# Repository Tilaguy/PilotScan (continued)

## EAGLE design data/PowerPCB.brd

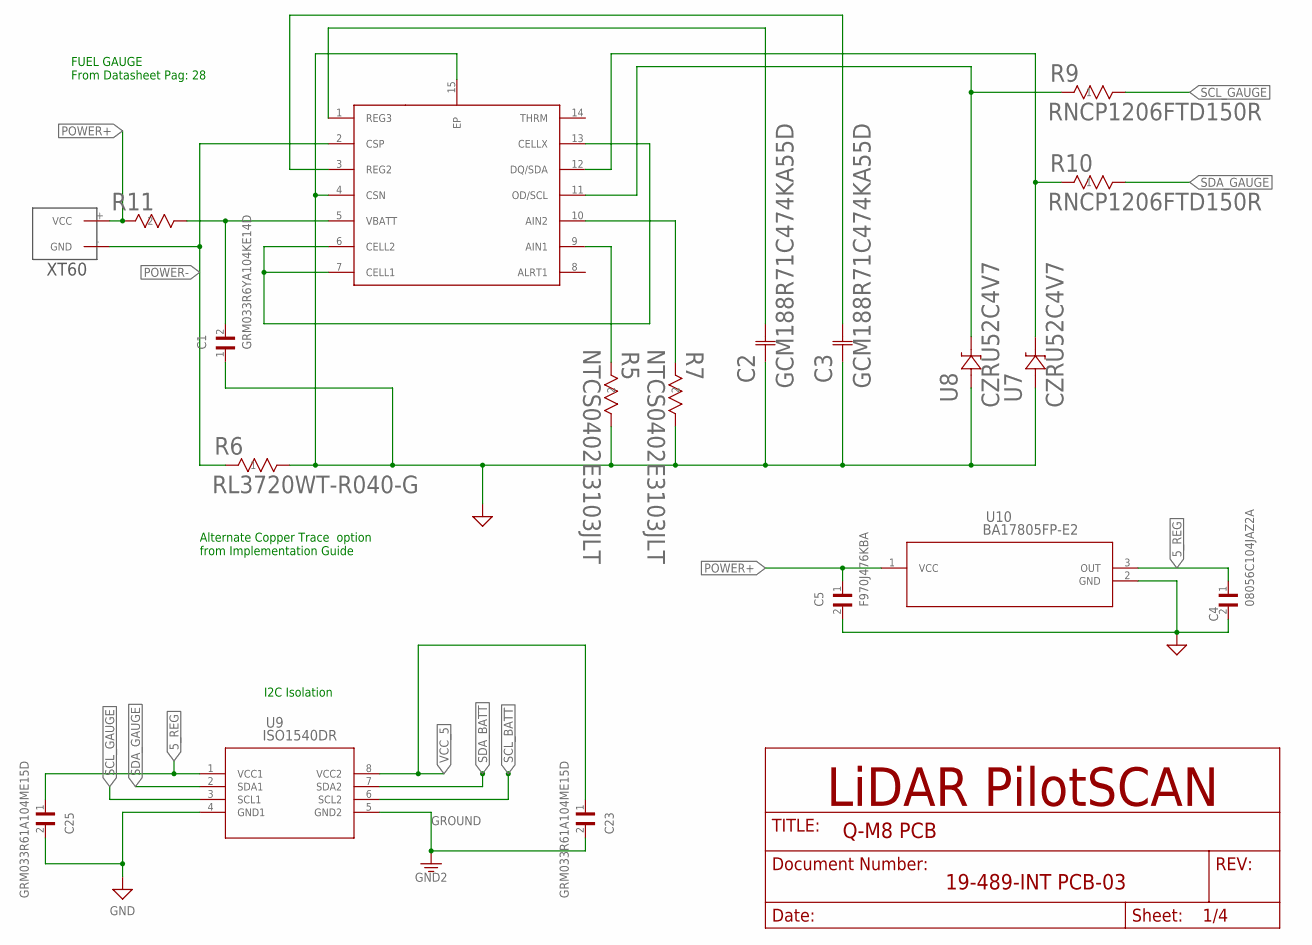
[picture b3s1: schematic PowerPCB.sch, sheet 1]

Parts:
C1: GRM033R6YA104KE14D; CAPC0603X33N
C2, C3: GCM188R71C474KA55D; G-188
C4: 08056C104JAZ2A; CAPC2012X140N
C5: F970J476KBA; CAPPC3528X210N
C23, C25: GRM033R61A104ME15D; CAPC0603X33N
J5: XT60
R5, R7: NTCS0402E3103JLT; RES_0402_NTC
R6: RL3720WT-R040-G; RES_2037
R9, R10: RNCP1206FTD150R; STA_RNCP1206
R11: ERA-2AKD100X; RC0402N
U5: MAX17205G+T
U7, U8: CZRU52C4V7; CZRU
U9: ISO1540DR; D8
U10: BA17805FP-E2; TO252-3

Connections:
5_REG: C4.1, C25.1, U9.1 (VCC1), U10.3 (OUT); also elsewhere on the board
GND: C1.1, C2.1, C3.1, C4.2, C5.2, C25.2, R5.1, R6.2, R7.1, U5.4 (CSN), U5.15 (EP), U7.2, U8.2, U9.4 (GND1), U10.2 (GND); also elsewhere on the board
GROUND: C23.2, U9.5 (GND2); also elsewhere on the board
unnamed: C1.2, R11.1, U5.5 (VBATT)
unnamed: R5.2, U5.9 (AIN1)
unnamed: C2.2, U5.1 (REG3)
unnamed: R7.2, U5.10 (AIN2)
unnamed: C3.2, U5.3 (REG2)
unnamed: U5.6 (CELL2), U5.7 (CELL1), U5.13 (CELLX)
unnamed: R9.1, U5.11 (OD/SCL), U8.1
unnamed: R10.1, U5.12 (DQ/SDA), U7.1
POWER+: C5.1, J5.+ (VCC), R11.2, U10.1 (VCC); also elsewhere on the board
POWER-: J5.- (GND), R6.1, U5.2 (CSP)
SCL_BATT: U9.6 (SCL2); also elsewhere on the board
SCL_GAUGE: R9.2, U9.3 (SCL1)
SDA_BATT: U9.7 (SDA2); also elsewhere on the board
SDA_GAUGE: R10.2, U9.2 (SDA1)
VCC_5: C23.1, U9.8 (VCC2); also elsewhere on the board

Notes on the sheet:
FUEL GAUGE From Datasheet Pag: 28
I2C Isolation
Alternate Copper Trace option from Implementation Guide

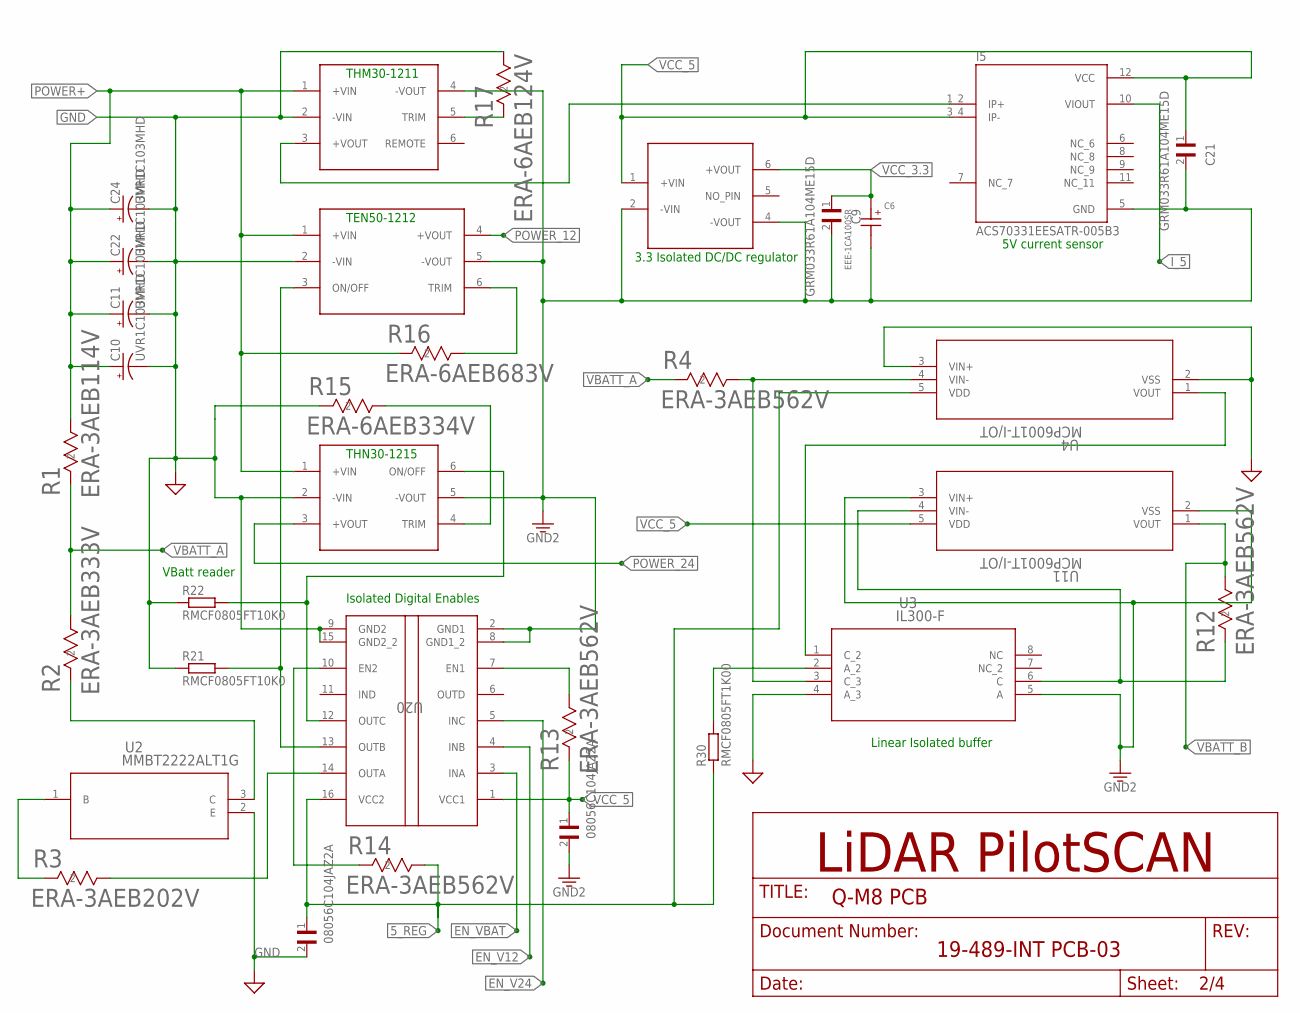
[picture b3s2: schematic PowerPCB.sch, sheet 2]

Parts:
C6: EEE-1CA100SR; CAPAE430X550N
C7, C8: 08056C104JAZ2A; CAPC2012X140N
C9, C21: GRM033R61A104ME15D; CAPC0603X33N
C10, C11, C22, C24: UVR1C103MHD; U1-PP
DCDC5: THM30-1211
DCDC12: TEN50-1212
DCDC24: THN30-1215
I5: ACS70331EESATR-005B3; ACS70331EESATR-2P5U3
R1: ERA-3AEB114V; RC0603N
R2: ERA-3AEB333V; RC0603N
R3: ERA-3AEB202V; RC0603N
R4, R12, R13, R14: ERA-3AEB562V; RC0603N
R15: ERA-6AEB334V; RC0805N
R16: ERA-6AEB683V; RC0805N
R17: ERA-6AEB124V; RC0805N
R21, R22: RMCF0805FT10K0
R30: RMCF0805FT1K00
U2: MMBT2222ALT1G; SOT-23
U3: IL300-F; DIP8_IL
U4, U11: MCP6001T-I/OT; SOT-23-5_MC
U6: TMV0503SHI
U20: ISO7741DBQR; DBQ0016A_N

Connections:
5_REG: C8.1, R14.1, R30.1, U4.5 (VDD), U20.16 (VCC2); also elsewhere on the board
EN_V12: U20.4 (INB); also elsewhere on the board
EN_V24: U20.5 (INC); also elsewhere on the board
EN_VBAT: U20.3 (INA); also elsewhere on the board
GND: C8.2, C10.2 (-), C11.2 (-), C22.2 (-), C24.2 (-), DCDC5.2 (-VIN), DCDC12.2 (-VIN), DCDC24.2 (-VIN), R15.2, R17.1, R21.1, R22.1, U2.2 (E), U3.4 (A_3), U4.2 (VSS), U4.3 (VIN+), U20.9 (GND2), U20.15 (GND2_2); also elsewhere on the board
GROUND: C6.2, C7.2, C9.2, C21.2, DCDC5.4 (-VOUT), DCDC12.5 (-VOUT), DCDC24.5 (-VOUT), I5.5 (GND), U3.5 (A), U6.2 (-VIN), U6.4 (-VOUT), U11.2 (VSS), U11.3 (VIN+), U20.2 (GND1), U20.8 (GND1_2); also elsewhere on the board
I_5: I5.10 (VIOUT); also elsewhere on the board
unnamed: R13.1, U20.7 (EN1)
unnamed: R3.2, U2.1 (B)
unnamed: R2.2, U2.3 (C)
unnamed: R4.1, U3.3 (C_3), U4.4 (VIN-)
unnamed: DCDC12.3 (ON/OFF), R21.2, U20.13 (OUTB)
unnamed: R30.2, U3.2 (A_2)
unnamed: R14.2, U20.10 (EN2)
unnamed: U3.1 (C_2), U4.1 (VOUT)
unnamed: R12.2, U3.6 (C), U11.4 (VIN-)
unnamed: DCDC24.6 (ON/OFF), R22.2, U20.12 (OUTC)
unnamed: R3.1, U20.14 (OUTA)
unnamed: DCDC5.5 (TRIM), R17.2
unnamed: DCDC24.4 (TRIM), R15.1
unnamed: DCDC12.6 (TRIM), R16.1
POWER+: C10.1 (+), C11.1 (+), C22.1 (+), C24.1 (+), DCDC5.1 (+VIN), DCDC12.1 (+VIN), DCDC24.1 (+VIN), R1.1, R16.2; also elsewhere on the board
POWER_5: DCDC5.3 (+VOUT), I5.1_2 (IP+)
POWER_12: DCDC12.4 (+VOUT); also elsewhere on the board
POWER_24: DCDC24.3 (+VOUT); also elsewhere on the board
VBATT_A: R1.2, R2.1, R4.2
VBATT_B: R12.1, U11.1 (VOUT); also elsewhere on the board
VCC_3.3: C6.1, C9.1, U6.6 (+VOUT); also elsewhere on the board
VCC_5: C7.1, C21.1, I5.3_4 (IP-), I5.12 (VCC), R13.2, U6.1 (+VIN), U11.5 (VDD), U20.1 (VCC1); also elsewhere on the board

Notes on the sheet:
Isolated Digital Enables
Linear Isolated buffer
5V current sensor
3.3 Isolated DC/DC regulator
VBatt reader
THM30-1211
THN30-1215
TEN50-1212

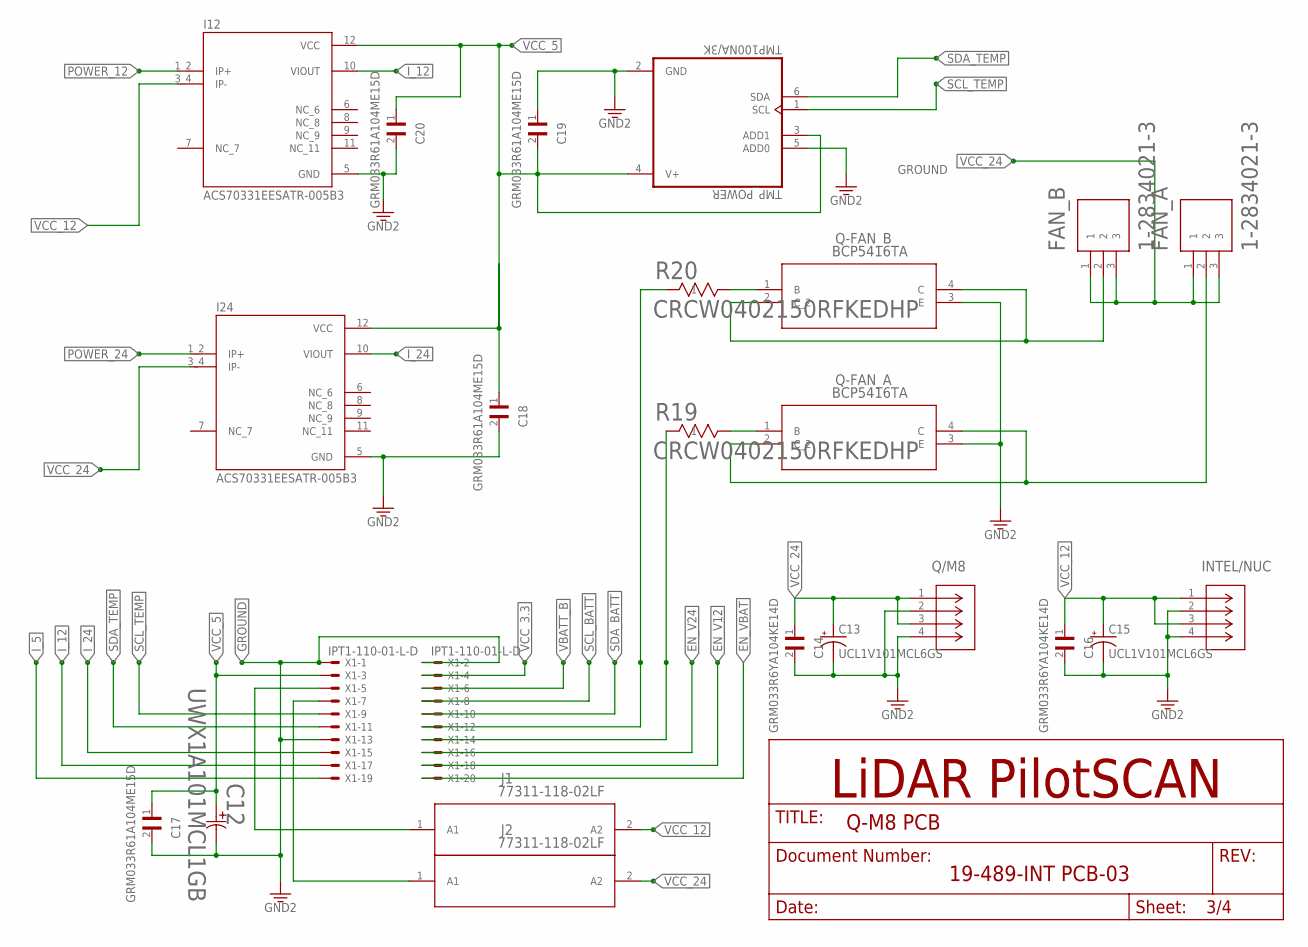
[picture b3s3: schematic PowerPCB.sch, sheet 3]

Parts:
C12: UWX1A101MCL1GB; PCAP_6.3X5.4-ELECT
C13, C15: UCL1V101MCL6GS; U2-K
C14, C16: GRM033R6YA104KE14D; CAPC0603X33N
C17, C18, C19, C20: GRM033R61A104ME15D; CAPC0603X33N
FAN_A: 1-2834021-3; CONN_1-2834021-3
FAN_B: 1-2834021-3; CONN_1-2834021-3
I12, I24: ACS70331EESATR-005B3; ACS70331EESATR-2P5U3
INTEL/NUC: 3-794630-4; CON4_2X2_P3MM_VMNL2
J1, J2: 77311-118-02LF
Q-FAN_A: BCP5416TA; SOT-223
Q-FAN_B: BCP5416TA; SOT-223
Q/M8: 3-794630-4; CON4_2X2_P3MM_VMNL2
R19, R20: CRCW0402150RFKEDHP; RES_CRCW_0402
TMP_POWER: TMP100NA/3K
X1: IPT1-110-01-L-D

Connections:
EN_V12: X1.P$18; also elsewhere on the board
EN_V24: X1.P$16; also elsewhere on the board
EN_VBAT: X1.P$20; also elsewhere on the board
GROUND: C12.2, C13.2 (-), C14.2, C15.2 (-), C16.2, C17.2, C18.2, C19.1, C20.2, I12.5 (GND), I24.5 (GND), INTEL/NUC.2, INTEL/NUC.4, Q-FAN_A.3 (E), Q-FAN_B.3 (E), Q/M8.2, Q/M8.4, TMP_POWER.2 (GND), TMP_POWER.5 (ADD0), X1.P$1, X1.P$2, X1.P$13; also elsewhere on the board
I_5: X1.P$19; also elsewhere on the board
I_12: I12.10 (VIOUT), X1.P$17
I_24: I24.10 (VIOUT), X1.P$15
unnamed: J1.1 (A1), X1.P$5
unnamed: J2.1 (A1), X1.P$7
unnamed: FAN_A.2, Q-FAN_A.2 (C_2), Q-FAN_A.4 (C)
unnamed: R20.1, X1.P$12
unnamed: R19.1, X1.P$14
unnamed: Q-FAN_B.1 (B), R20.2
unnamed: Q-FAN_A.1 (B), R19.2
unnamed: FAN_B.2, Q-FAN_B.2 (C_2), Q-FAN_B.4 (C)
POWER_12: I12.1_2 (IP+); also elsewhere on the board
POWER_24: I24.1_2 (IP+); also elsewhere on the board
SCL_BATT: X1.P$8; also elsewhere on the board
SCL_TEMP: TMP_POWER.1 (SCL), X1.P$9
SDA_BATT: X1.P$10; also elsewhere on the board
SDA_TEMP: TMP_POWER.6 (SDA), X1.P$11
VBATT_B: X1.P$6; also elsewhere on the board
VCC_3.3: X1.P$4; also elsewhere on the board
VCC_5: C12.1, C17.1, C18.1, C19.2, C20.1, I12.12 (VCC), I24.12 (VCC), TMP_POWER.3 (ADD1), TMP_POWER.4 (V+), X1.P$3; also elsewhere on the board
VCC_12: C15.1 (+), C16.1, I12.3_4 (IP-), INTEL/NUC.1, INTEL/NUC.3, J1.2 (A2); also elsewhere on the board
VCC_24: C13.1 (+), C14.1, FAN_A.1, FAN_A.3, FAN_B.1, FAN_B.3, I24.3_4 (IP-), J2.2 (A2), Q/M8.1, Q/M8.3; also elsewhere on the board

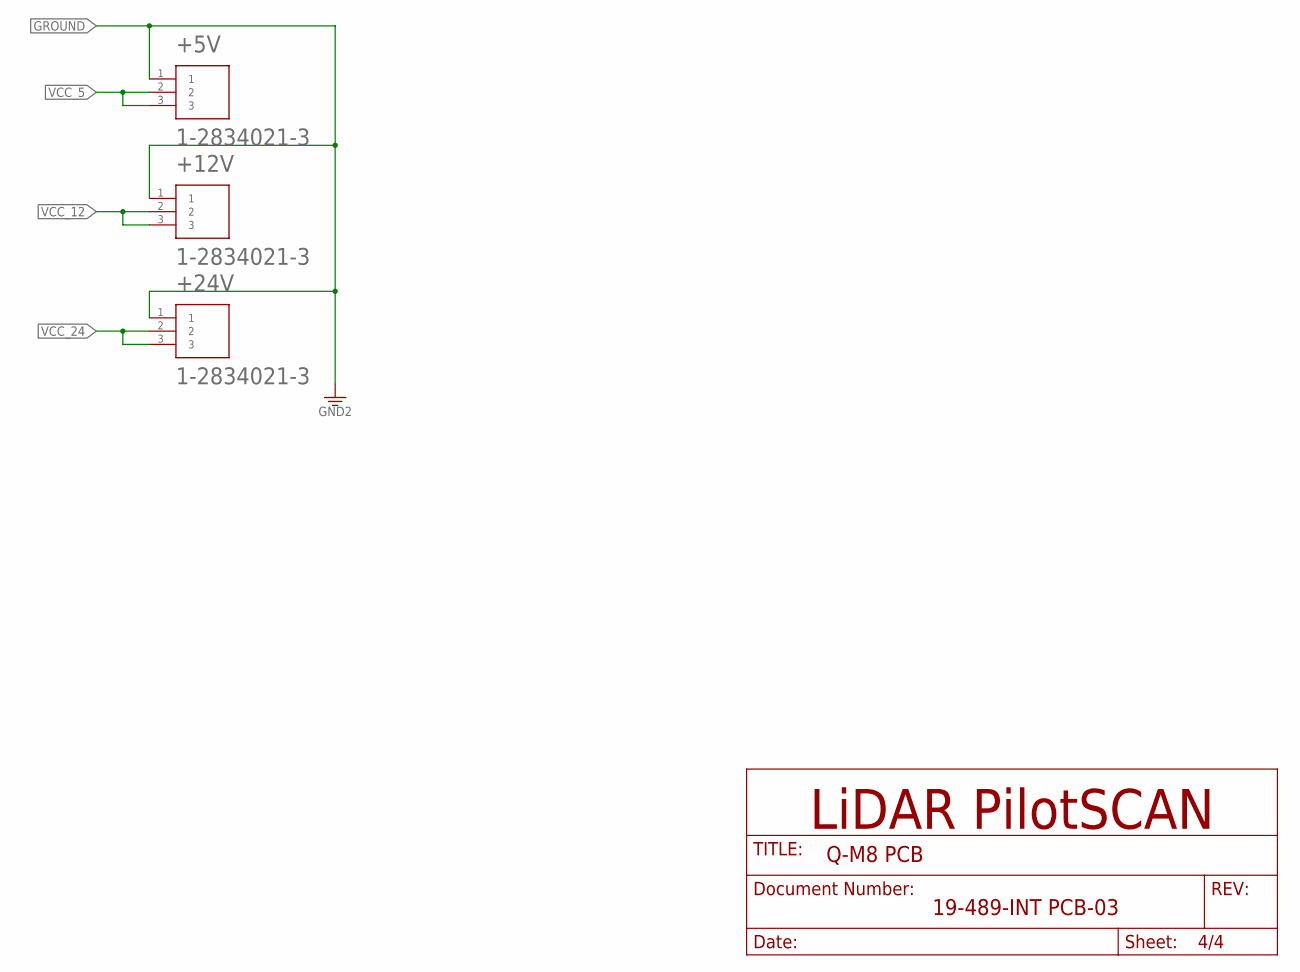
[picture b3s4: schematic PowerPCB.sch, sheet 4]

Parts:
+5V, +12V, +24V: 1-2834021-3; CONN_1-2834021-3

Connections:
GROUND: +5V.1, +12V.1, +24V.1; also elsewhere on the board
VCC_5: +5V.2, +5V.3; also elsewhere on the board
VCC_12: +12V.2, +12V.3; also elsewhere on the board
VCC_24: +24V.2, +24V.3; also elsewhere on the board

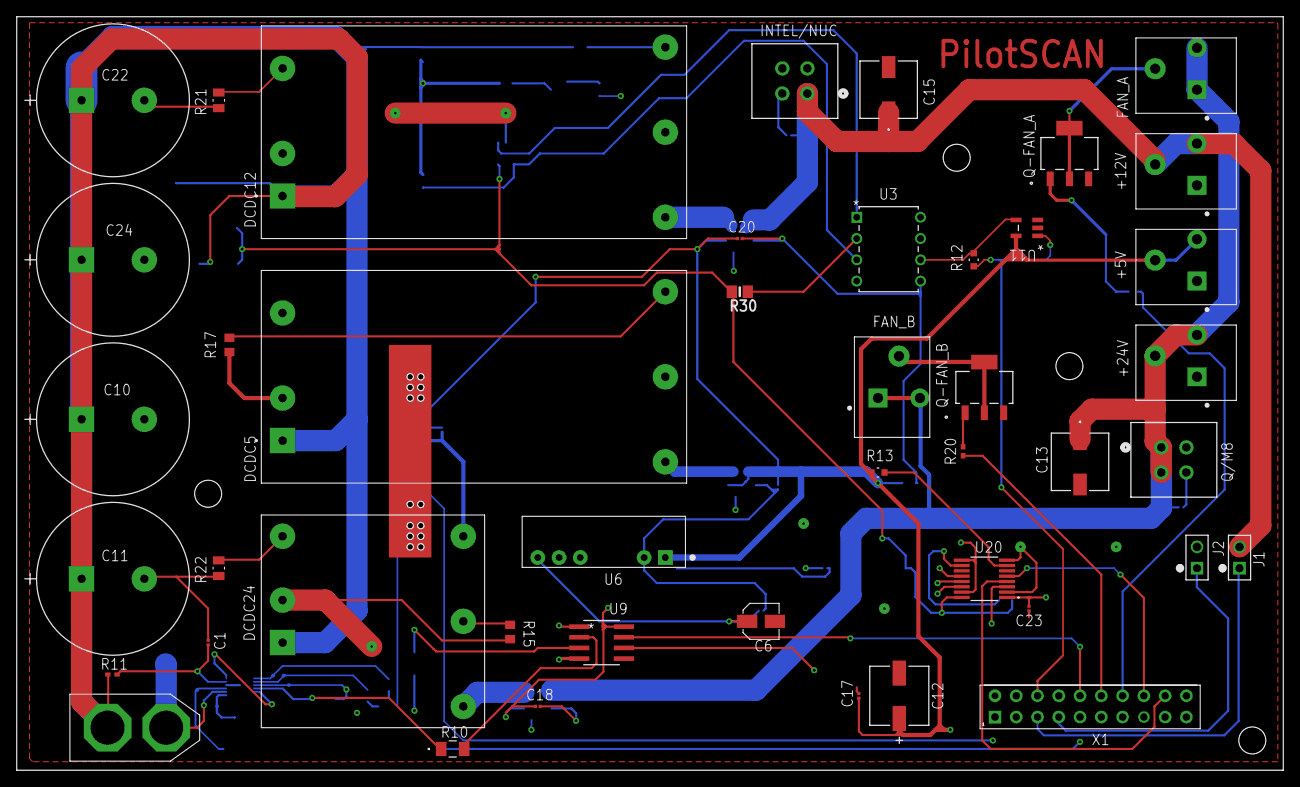
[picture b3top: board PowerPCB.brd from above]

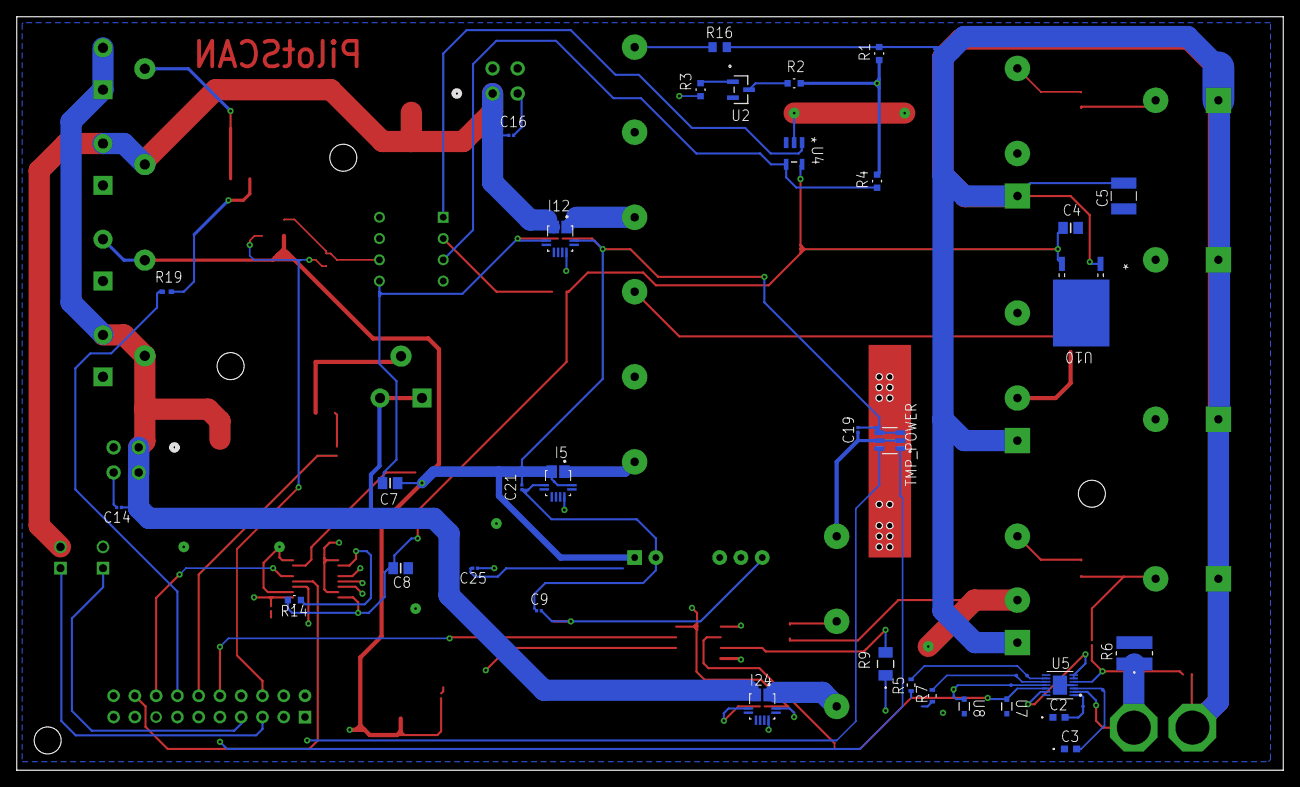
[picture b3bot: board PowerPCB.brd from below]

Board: 4 copper layers, 151.3 x 90.0 mm, 77 parts (33 on the bottom side), 56 nets.

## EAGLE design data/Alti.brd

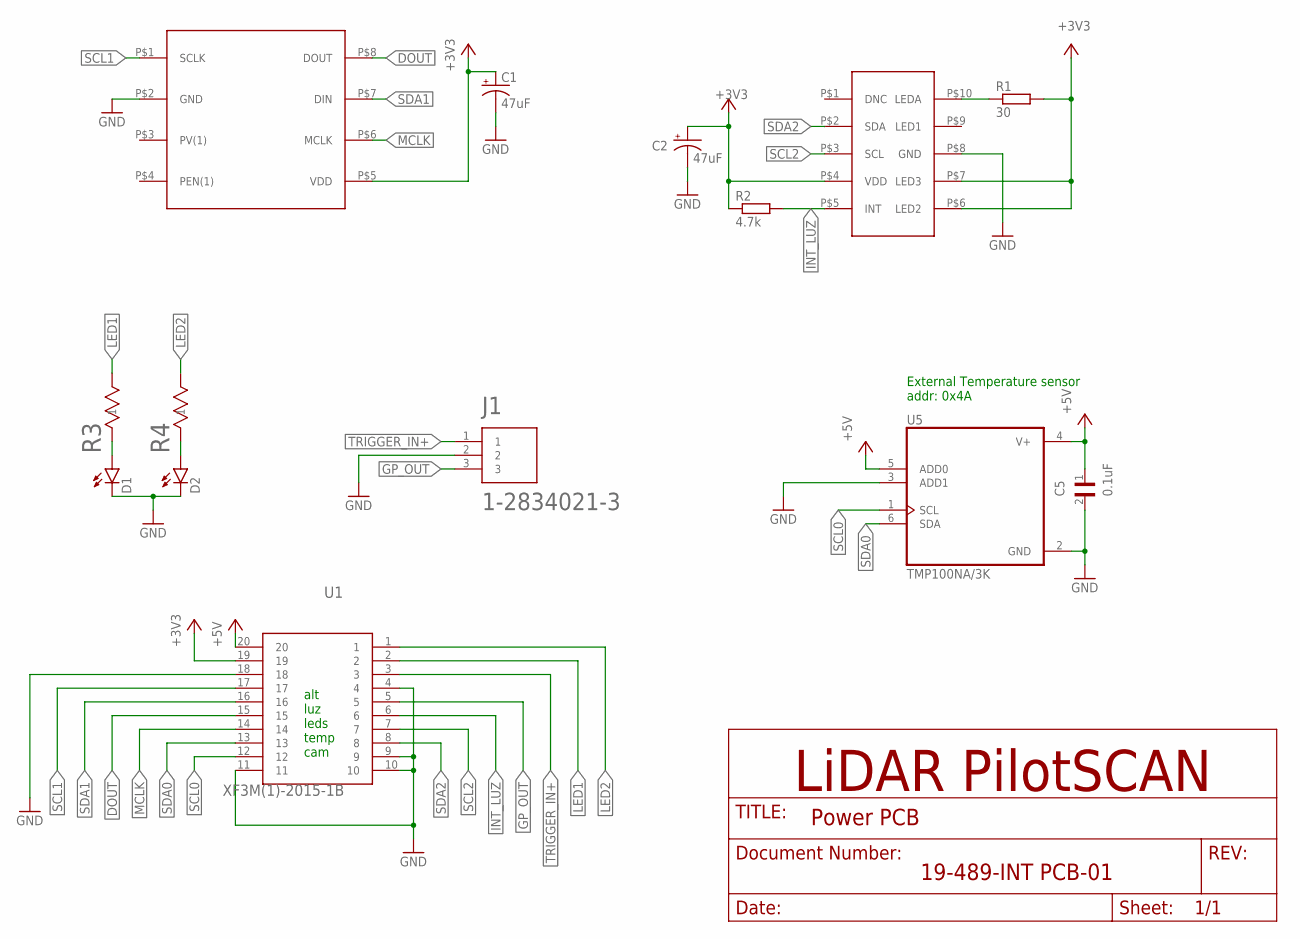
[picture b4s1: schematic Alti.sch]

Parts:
C1, C2: 47uF; CL31A476MQHNNWE
C5: 0.1uF; CAPC2012X140N
D1, D2: TLMS1000-GS08; RESC1608X55
J1: 1-2834021-3; CONN_1-2834021-3
R1: 30; 1812X7R
R2: 4.7k; RMCF0805FT4K70
R3, R4: RC0201JR-071K8L; RES_RC0201_P6XP3
U1: XF3M(1)-2015-1B
U2: 325540009-50
U3: SI1147-M01-GM
U5: TMP100NA/3K

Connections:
+3V3: C1.2 (+), C2.2 (+), R1.2, R2.1, U1.19, U2.P$5 (VDD), U3.P$4 (VDD), U3.P$6 (LED2), U3.P$7 (LED3)
+5V: C5.1, U1.20, U5.4 (V+), U5.5 (ADD0)
DOUT: U1.15, U2.P$8 (DOUT)
GND: C1.1 (-), C2.1 (-), C5.2, D1.2 (C), D2.2 (C), J1.2, U1.4, U1.9, U1.10, U1.11, U1.18, U2.P$2 (GND), U3.P$8 (GND), U5.2 (GND), U5.3 (ADD1)
GP_OUT: J1.3, U1.5
INT_LUZ: R2.2, U1.6, U3.P$5 (INT)
LED1: R3.2, U1.2
LED2: R4.2, U1.1
MCLK: U1.14, U2.P$6 (MCLK)
unnamed: D1.1 (A), R3.1
unnamed: D2.1 (A), R4.1
unnamed: R1.1, U3.P$10 (LEDA)
SCL0: U1.12, U5.1 (SCL)
SCL1: U1.17, U2.P$1 (SCLK)
SCL2: U1.7, U3.P$3 (SCL)
SDA0: U1.13, U5.6 (SDA)
SDA1: U1.16, U2.P$7 (DIN)
SDA2: U1.8, U3.P$2 (SDA)
TRIGGER_IN+: J1.1, U1.3

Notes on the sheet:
alt luz leds temp cam
External Temperature sensor addr: 0x4A

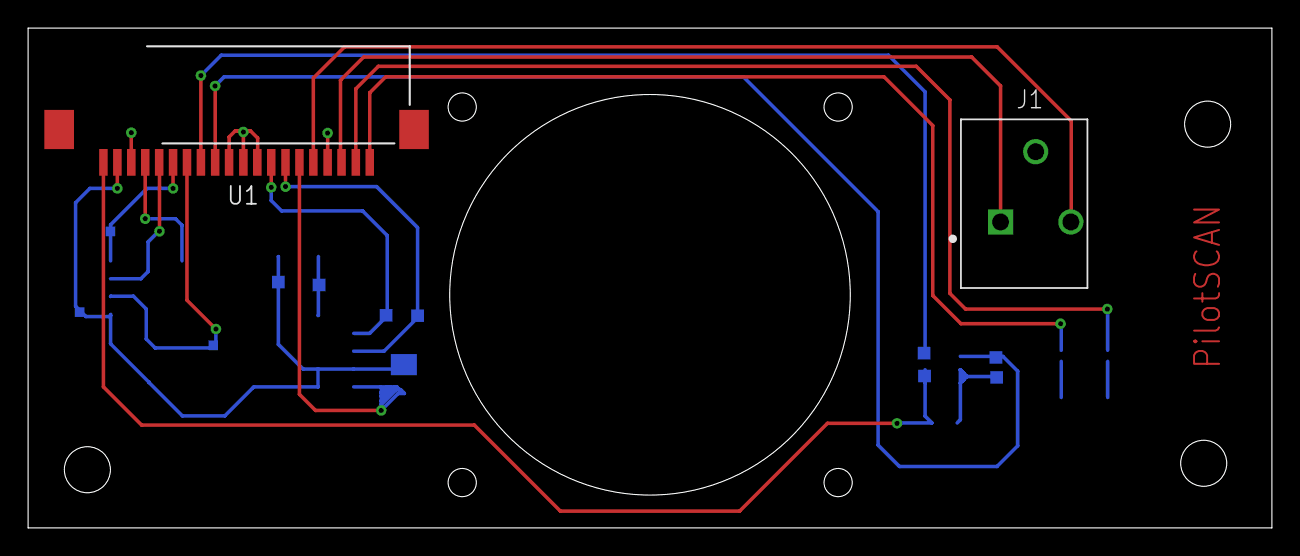
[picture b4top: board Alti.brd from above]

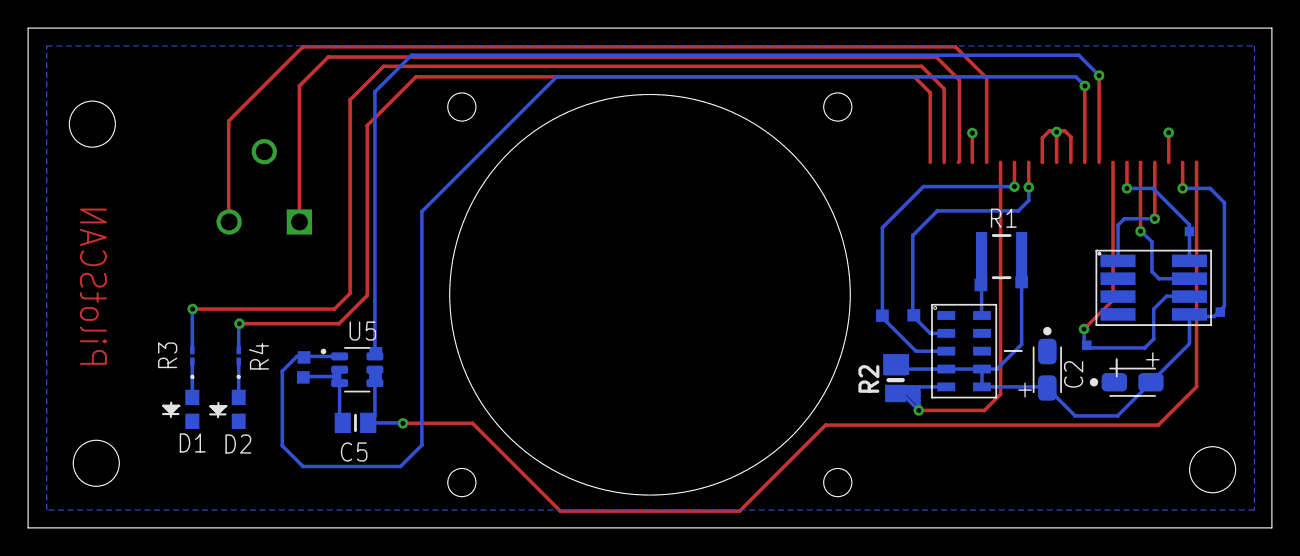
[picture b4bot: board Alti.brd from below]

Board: 2 copper layers, 88.5 x 35.6 mm, 14 parts (12 on the bottom side), 19 nets.

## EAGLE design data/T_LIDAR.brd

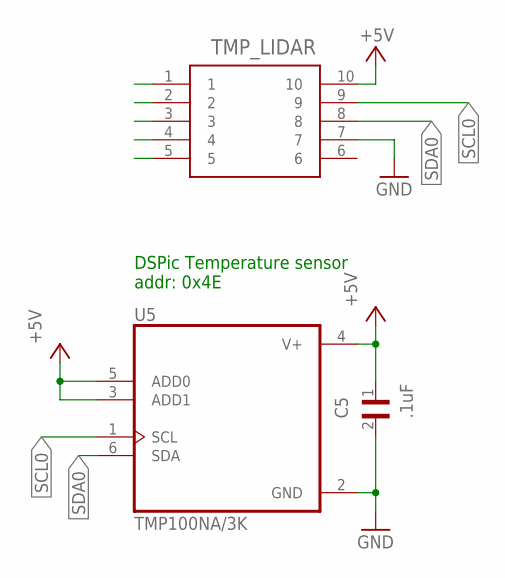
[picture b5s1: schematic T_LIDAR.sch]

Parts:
C5: .1uF; CAPC2012X140N
TMP_LIDAR: 522071060
U5: TMP100NA/3K

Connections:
+5V: C5.1, TMP_LIDAR.10, U5.3 (ADD1), U5.4 (V+), U5.5 (ADD0)
GND: C5.2, TMP_LIDAR.7, U5.2 (GND)
SCL0: TMP_LIDAR.9, U5.1 (SCL)
SDA0: TMP_LIDAR.8, U5.6 (SDA)

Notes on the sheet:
DSPic Temperature sensor addr: 0x4E

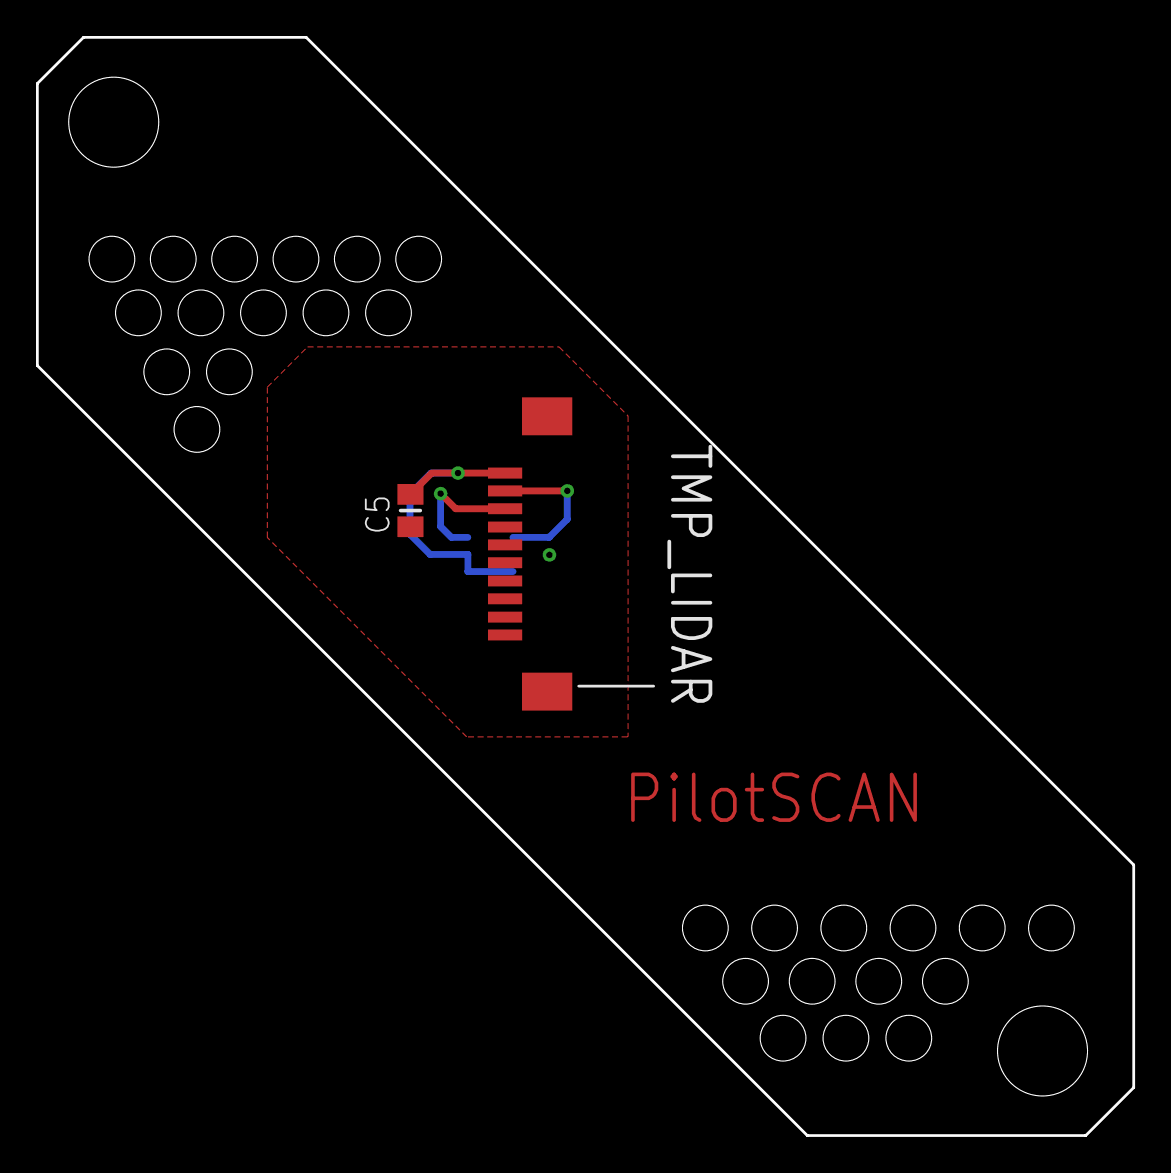
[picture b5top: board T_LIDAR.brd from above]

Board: 2 copper layers, 60.9 x 61.0 mm, 3 parts (1 on the bottom side), 4 nets.

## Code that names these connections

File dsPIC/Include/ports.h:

#use fast_io(B)
#use fast_io(C)
#use fast_io(D)
#use fast_io(E)
#use fast_io(F)

/********************************************/
// Flags
/********************************************/
int1 f_begin, f_error, f_conn=1;
char f_satar, f_conSta, HDD_error, RAM_error;
char R1,G1,B1,R2,G2,B2,R3,G3,B3,R4,G4,B4;			// Enter color valued in RGB
int cycles = 2;

void setup(){
	set_tris_B(0b00111111);
	set_tris_C(0b00111111);
	set_tris_D(0b11110100);
	set_tris_E(0b11011000);
//	set_tris_F(0b10111111);
}
/********************************************/
// Port definition
/********************************************/
#define CH_I5		0 		// PIN_B0
#define CH_I12		1 		// PIN_B1
#define CH_I24		2 		// PIN_B2
#define CH_24V		3 		// PIN_B3
#define CH_12V		4 		// PIN_B4
#define CH_05V		5 		// PIN_B5
#define CH_VBAT		6 		// PIN_B6
#define EN24		PIN_B7	// PIN 26
#define EN12		PIN_B8	// PIN 27
#define EN_VBAT		PIN_C15	// PIN 31
#define LED1		PIN_D0	// PIN 42
#define FAN_A		PIN_D1	// PIN 37
#define FAN_B		PIN_D3	// PIN 38
#define SPEAKER		PIN_E0	// PIN 15
#define LED_RGB		PIN_E1	// PIN 14
#define EN_ANA		PIN_E2	// PIN 11
#define Cap_bot		PIN_F0	// PIN 05
#define LED2		PIN_F6	// PIN 01
#define NUC_ON_OFF	PIN_E5	// PIN 08
#define NUC_LED		PIN_E4	// PIN 09

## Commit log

2020-01-17 Create a
2020-02-12 Rename README.md to README(Original).md
2020-03-20 Create Esquemáticos del Eagle
2021-01-23 23.01.2021
